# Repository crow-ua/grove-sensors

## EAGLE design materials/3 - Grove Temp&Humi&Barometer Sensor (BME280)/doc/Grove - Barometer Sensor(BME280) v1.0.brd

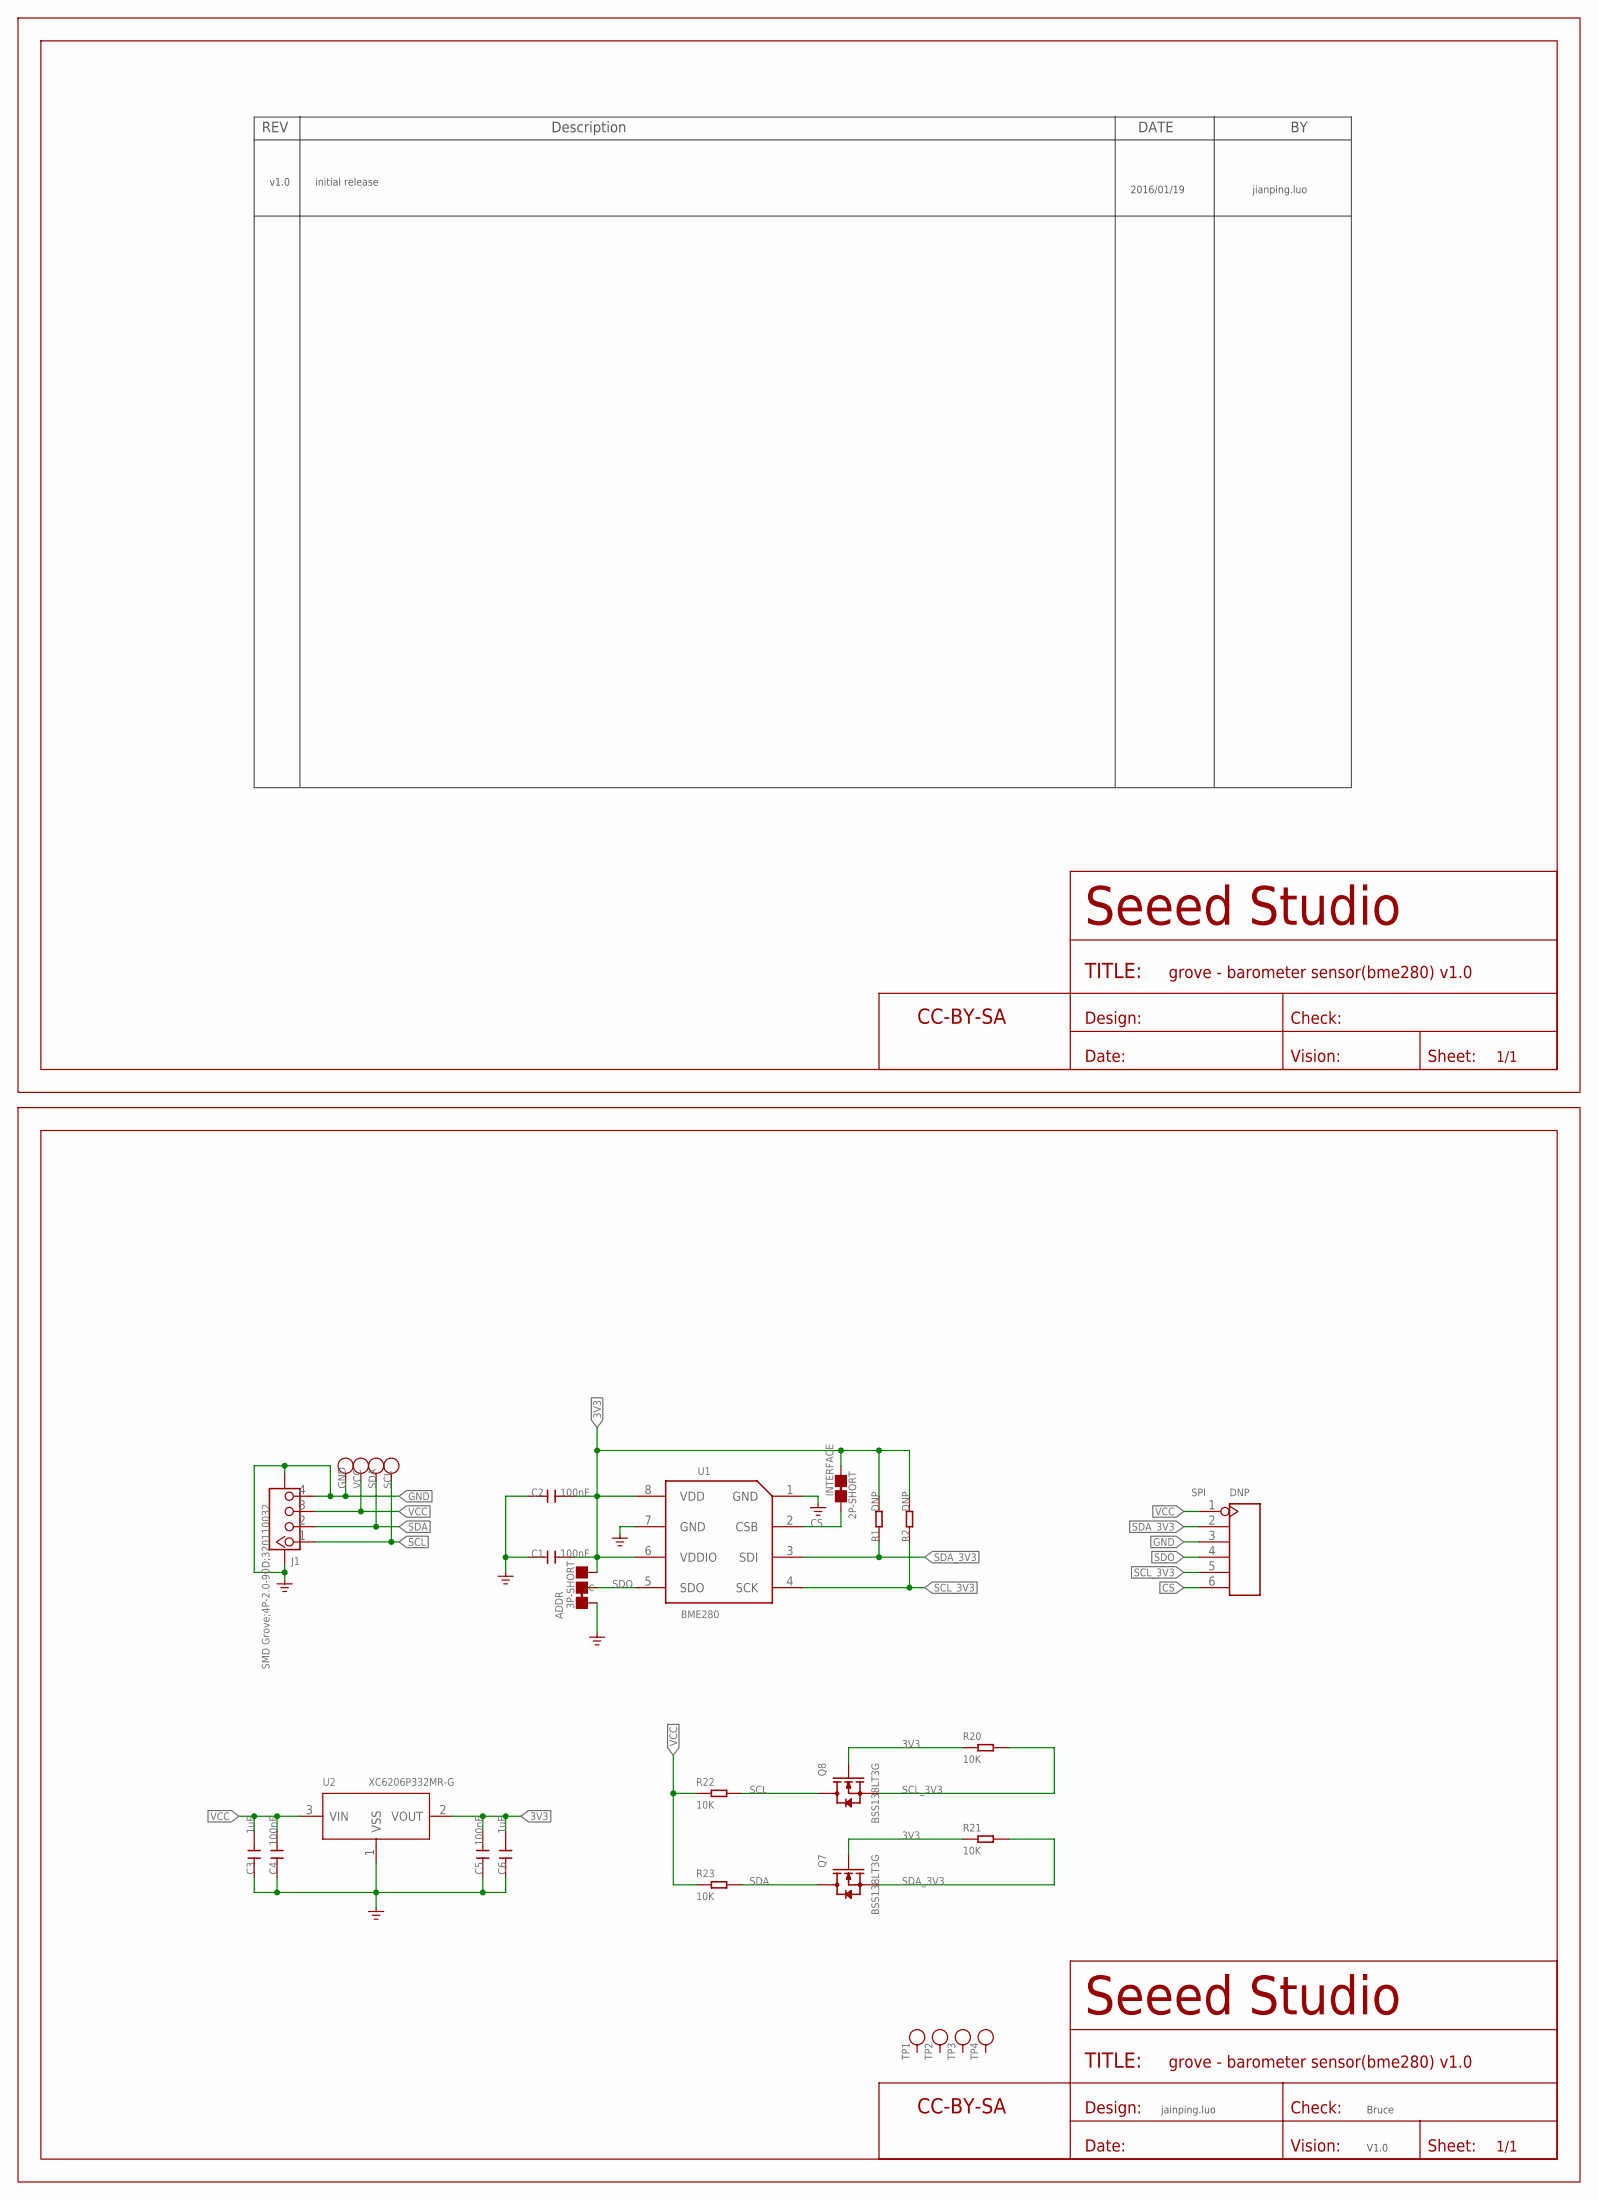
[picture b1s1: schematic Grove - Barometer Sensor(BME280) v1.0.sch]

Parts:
ADDR: 3P-SHORT; 3P-SMD-SHORT
C1, C2, C4, C5: 100nF; C0603
C3, C6: 1uF; C0603
FR1, FR2: SEEEDSTUDIO-OPEN-SCH-FRAME; SEEEDSTUDIO-PCB-FRAME
GND: TEST-POINT'4545'; TP-D45MIL
INTERFACE: 2P-SHORT; 2P-SMD-SHORT
J1: SMD Grove;4P-2.0-90D;320110032; HW4-SMD-2.0-90D
Q7, Q8: BSS138LT3G; SOT-23
R1, R2: DNP; R0603
R20, R21, R22, R23: 10K; R0603
SCL: TEST-POINT'4545'; TP-D45MIL
SDA: TEST-POINT'4545'; TP-D45MIL
SPI: DNP; H6-2.54-C65D35MIL
TP1, TP2, TP3, TP4: TEST-POINT'4545'; TP-D45MIL
U1: BME280; LGA8-0.65-2.5X2.5X0.95MM
U2: XC6206P332MR-G; SOT-23
VCC: TEST-POINT'4545'; TP-D45MIL

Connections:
3V3: ADDR.00 (R), C1.1, C2.1, C5.1, C6.1, INTERFACE.2, Q7.1 (G), Q8.1 (G), R1.2, R2.2, R20.1, R21.1, U1.6 (VDDIO), U1.8 (VDD), U2.2 (VOUT)
CS: INTERFACE.1, SPI.6, U1.2 (CSB)
GND: ADDR.11 (L), C1.2, C2.2, C3.2, C4.2, C5.2, C6.2, GND.T, J1.4, J1.SS1, J1.SS2, SPI.3, U1.1 (GND), U1.7 (GND), U2.1 (VSS)
SCL: J1.1, Q8.3 (D), R22.2, SCL.T
SCL_3V3: Q8.2 (S), R2.1, R20.2, SPI.5, U1.4 (SCK)
SDA: J1.2, Q7.3 (D), R23.2, SDA.T
SDA_3V3: Q7.2 (S), R1.1, R21.2, SPI.2, U1.3 (SDI)
SDO: ADDR.MM (C), SPI.4, U1.5 (SDO)
VCC: C3.1, C4.1, J1.3, R22.1, R23.1, SPI.1, U2.3 (VIN), VCC.T

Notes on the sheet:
v1.0
initial release
2016/01/19
jianping.luo
jainping.luo
Bruce
V1.0

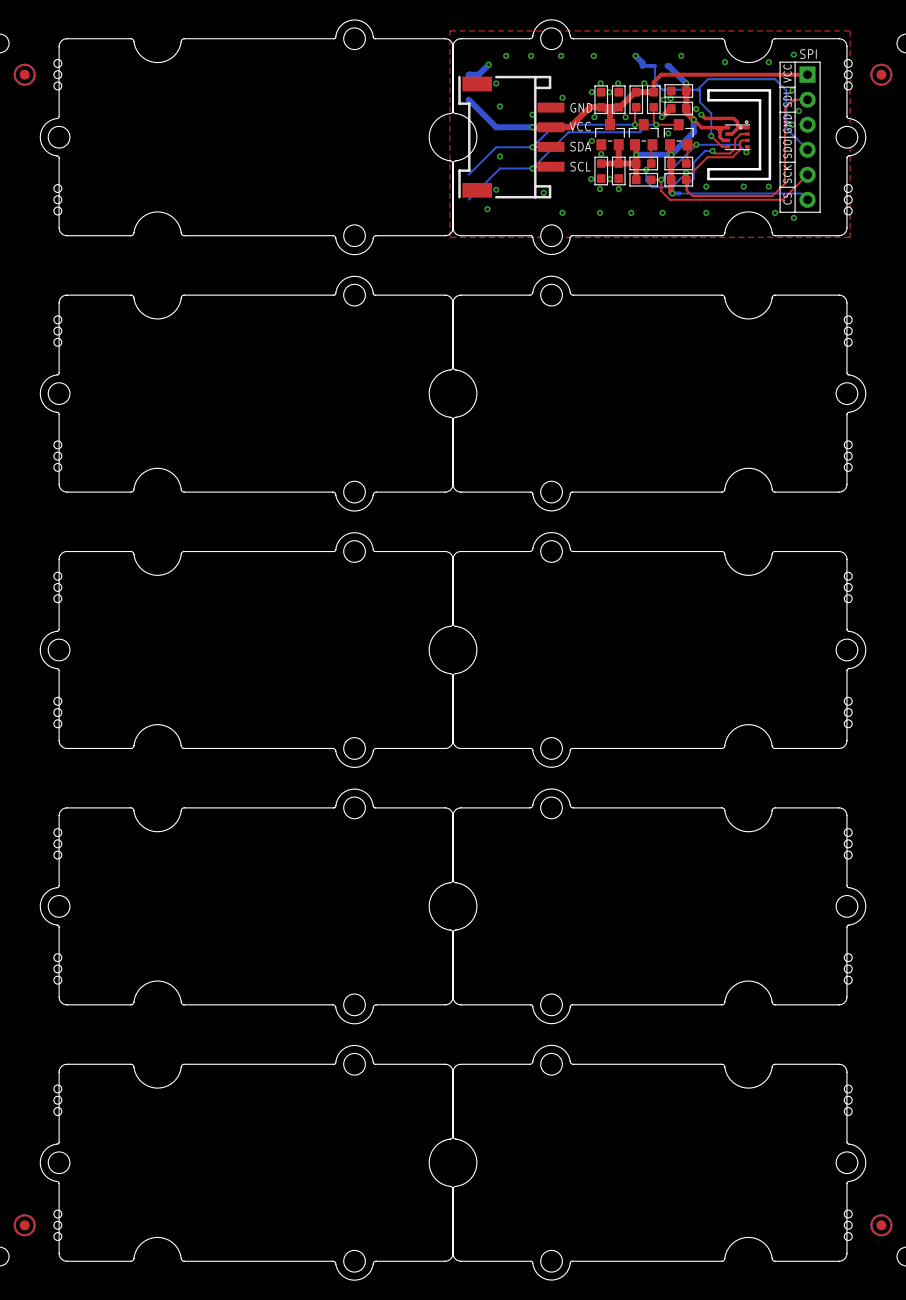
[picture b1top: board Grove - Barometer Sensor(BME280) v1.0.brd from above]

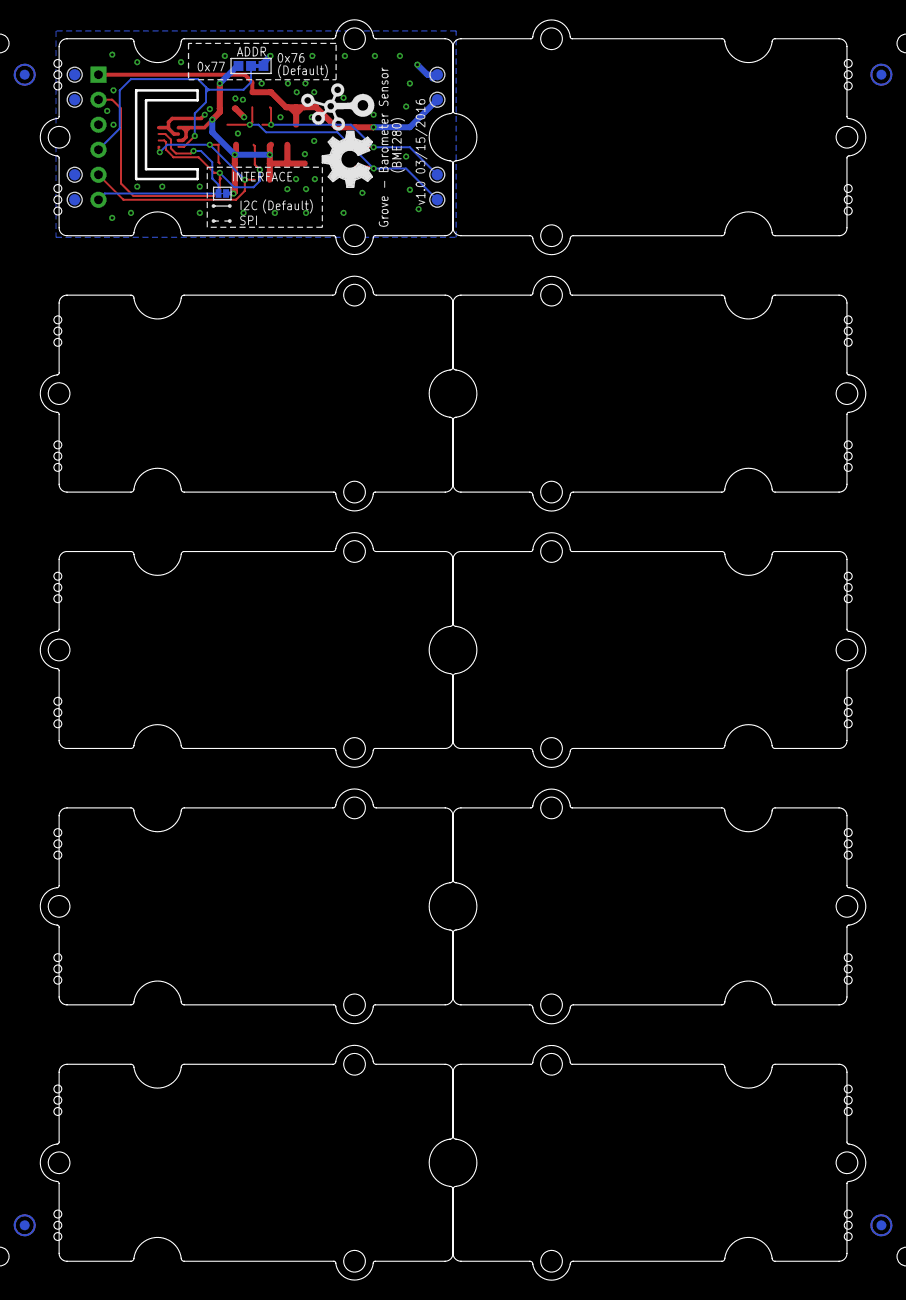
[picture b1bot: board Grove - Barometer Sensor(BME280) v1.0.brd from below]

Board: 2 copper layers, 83.8 x 128.0 mm, 50 parts (16 on the bottom side), 9 nets.

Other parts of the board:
P1, P2, P3, P4, P5, P6, P7, P8: ROUND-MARK-1.0
U3, U4, U5, U6, U7, U8, U9, U10, U11, U12: GROVE-TEST-PLATFORM
U$3: OSHW_FILLX200_NOTEXT
U$4: TWIGLOGO

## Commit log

2017-06-14 Added some references and source code for Grove sensors.

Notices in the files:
parts and their libraries:
moudle-new: This work is licensed under the Creative Commons Attribution 4.0 International License.
To view a copy of this license,visit:
http://creativecommons.org/licenses/by-sa/4.0
moudle-new: CC-BY-SA
